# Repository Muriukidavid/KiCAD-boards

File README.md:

My KiCAD boards

These are not final
Mostly Arduino breakout boards and shields

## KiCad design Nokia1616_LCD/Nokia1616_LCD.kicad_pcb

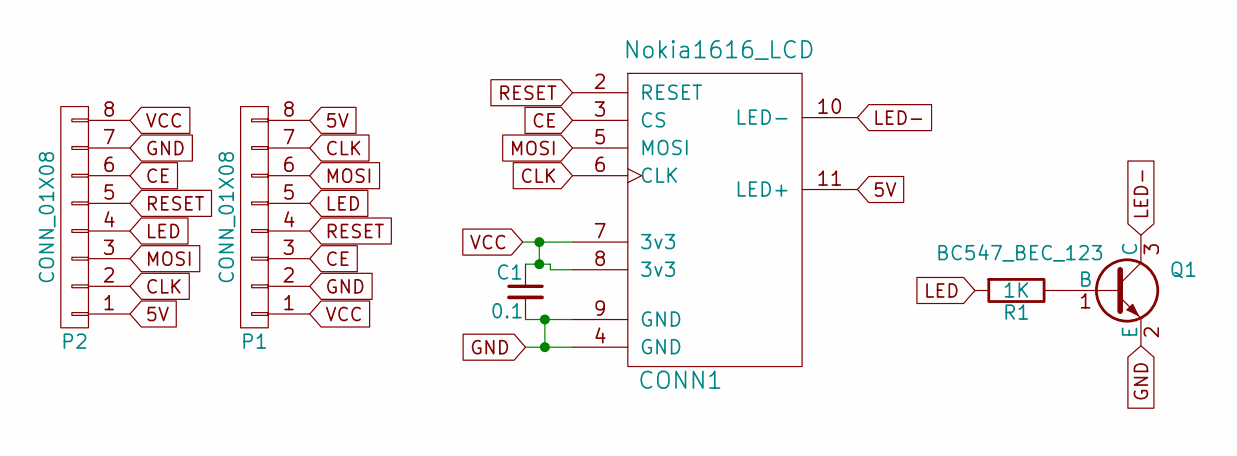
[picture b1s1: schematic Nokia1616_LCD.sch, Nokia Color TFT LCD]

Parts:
C1: 0.1; C_1206
CONN1: Nokia1616_LCD
P1, P2: CONN_01X08; Pin_Header_Straight_1x08_Pitch2.54mm
Q1: BC547_BEC_123; SOT-23
R1: 1K; R_1206

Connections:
5V: CONN1.11 (LED+), P1.8, P2.1
CE: CONN1.3 (CS), P1.3, P2.6
CLK: CONN1.6 (CLK), P1.7, P2.2
GND: C1.2, CONN1.4 (GND), CONN1.9 (GND), P1.2, P2.7, Q1.2 (E)
LED: P1.5, P2.4, R1.2
LED-: CONN1.10 (LED-), Q1.3 (C)
MOSI: CONN1.5 (MOSI), P1.6, P2.3
unnamed: Q1.1 (B), R1.1
RESET: CONN1.2 (RESET), P1.4, P2.5
VCC: C1.1, CONN1.7 (3v3), CONN1.8 (3v3), P1.1, P2.8

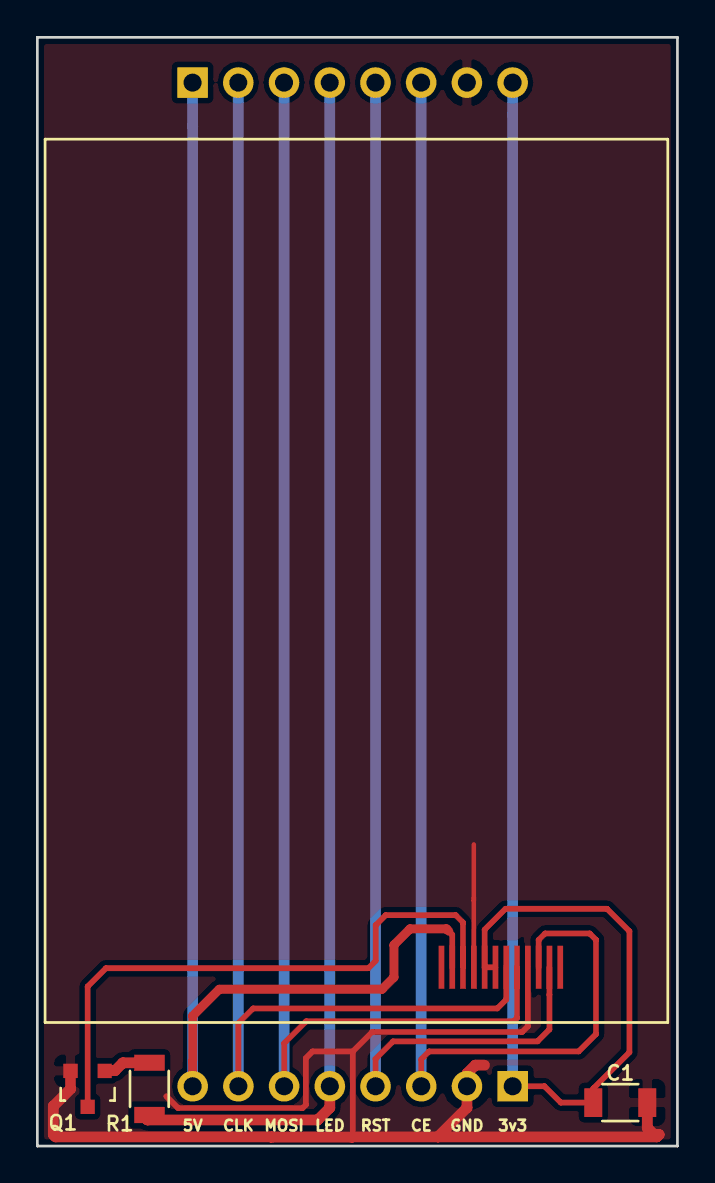
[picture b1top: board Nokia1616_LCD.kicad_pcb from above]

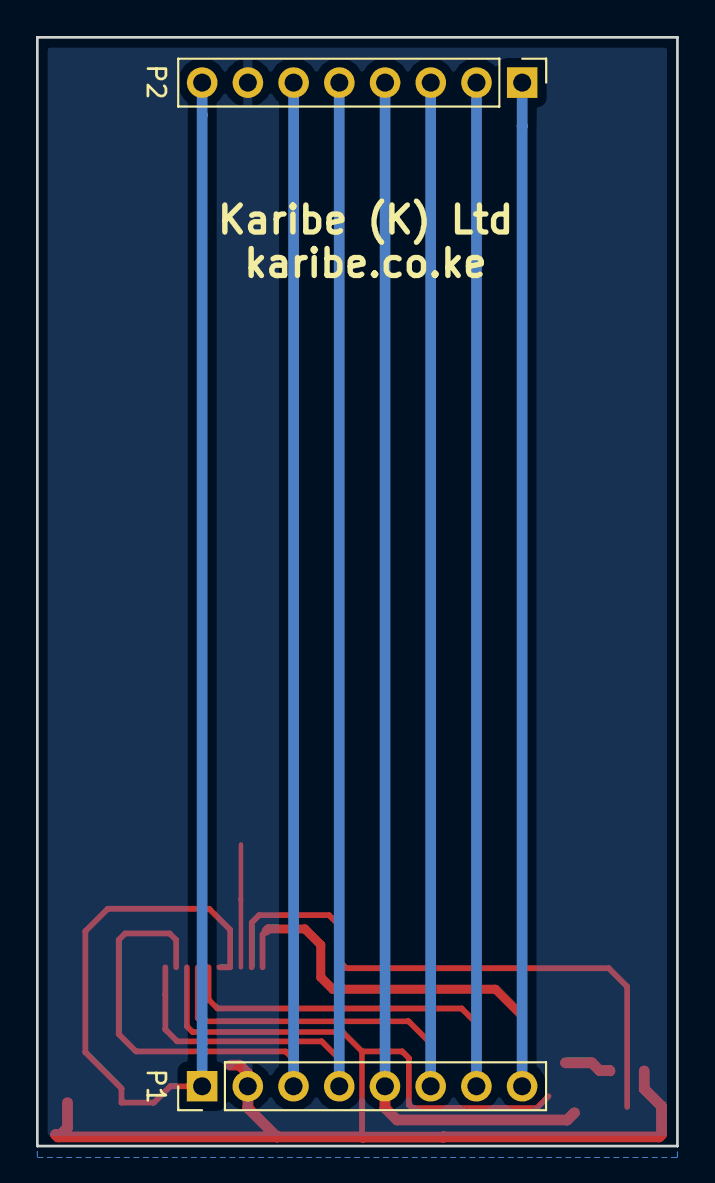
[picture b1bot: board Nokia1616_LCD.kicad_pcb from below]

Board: 2 copper layers, 35.6 x 61.6 mm, 6 parts (2 on the bottom side), 10 nets.

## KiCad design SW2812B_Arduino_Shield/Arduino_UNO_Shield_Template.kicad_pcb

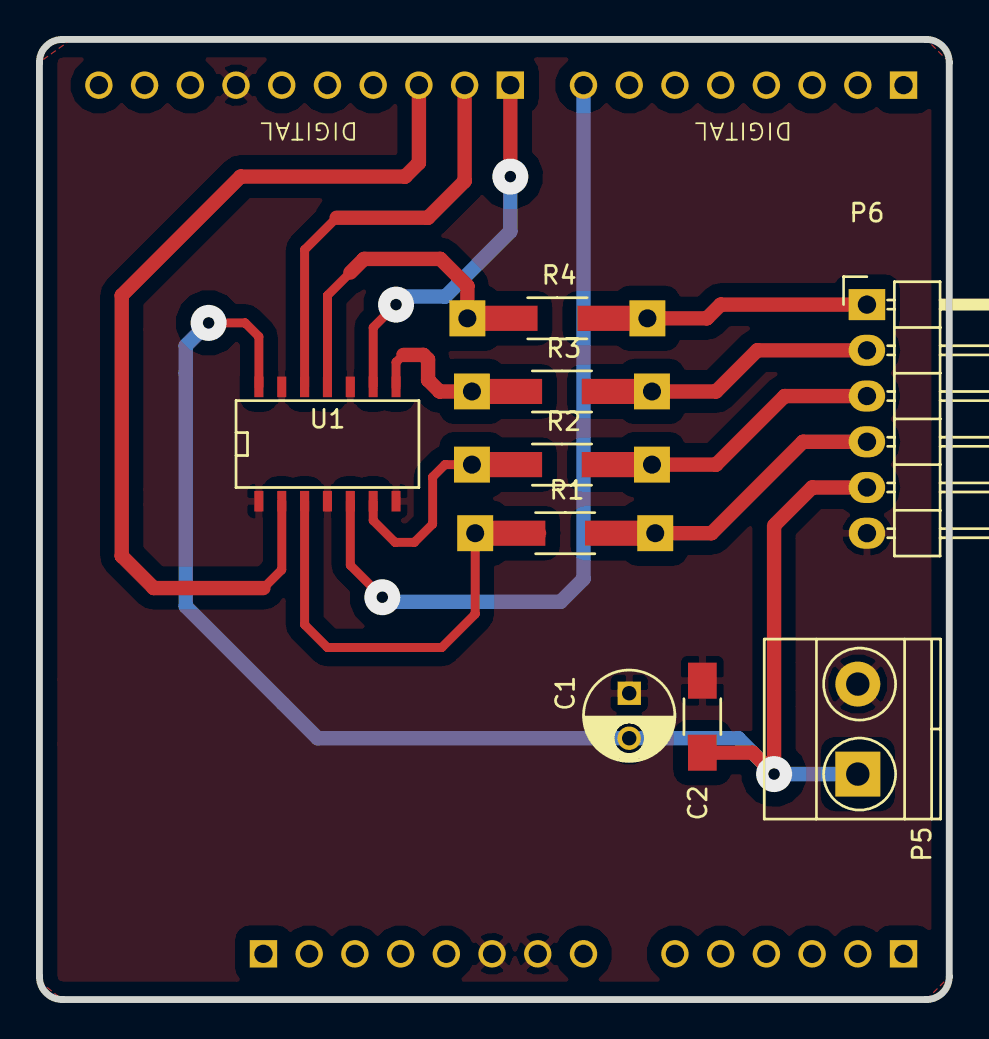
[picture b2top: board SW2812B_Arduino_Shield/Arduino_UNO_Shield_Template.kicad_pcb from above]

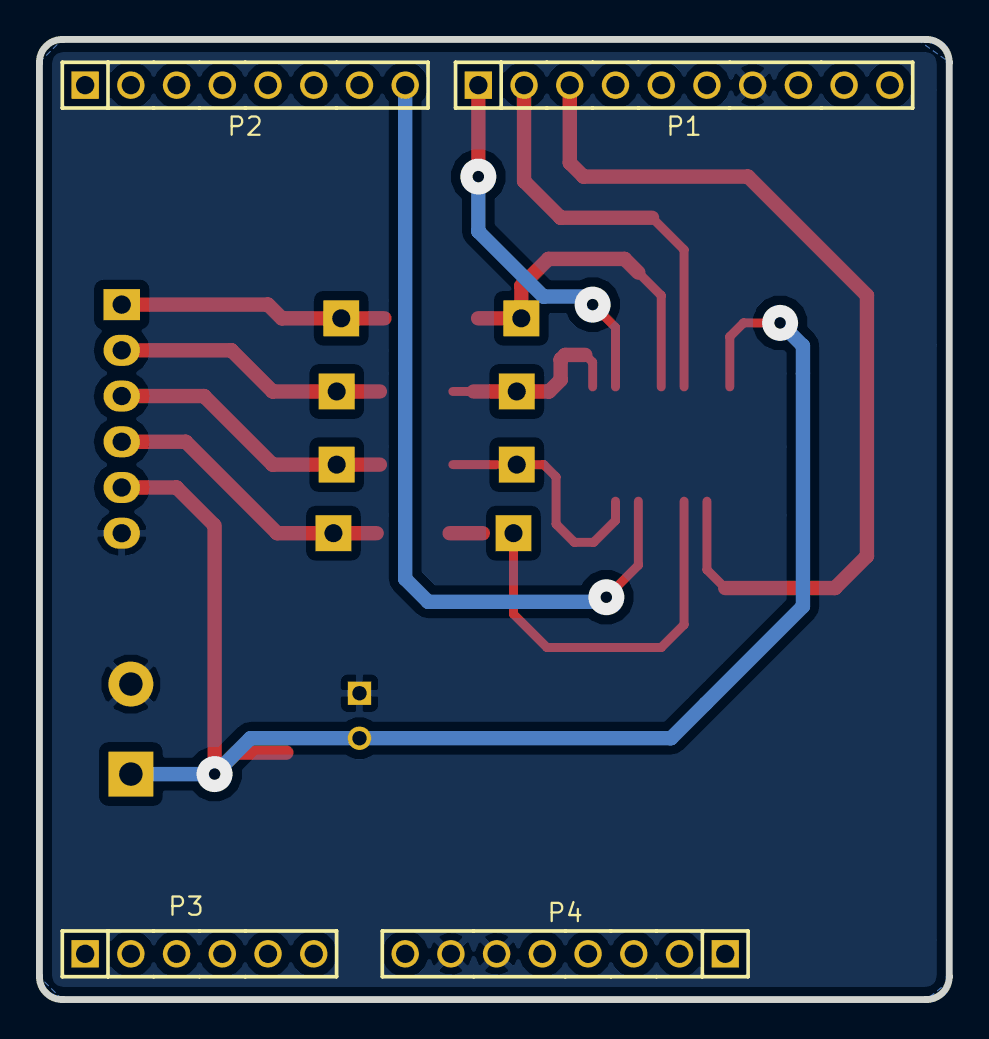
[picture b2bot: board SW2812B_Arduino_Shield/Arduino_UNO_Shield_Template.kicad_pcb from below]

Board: 2 copper layers, 50.5 x 53.3 mm, 13 parts (4 on the bottom side), 14 nets.

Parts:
C1: 1000uF; C_Radial_D5_L11_P2.5
C2: 1000uF; C_1206_HandSoldering
P1: HEADER_M_2.54MM_1R10P_ST_AU_PTH
P2, P4: HEADER_M_2.54MM_1R8P_ST_AU_PTH
P3: HEADER_M_2.54MM_1R6P_ST_AU_PTH
P5: CONN_01X02; TerminalBlock_Pheonix_MKDS1.5-2pol
P6: CONN_01X06; Pin_Header_Angled_1x06
R1, R2, R3, R4: R; Resistor_SMD+THTuniversal_1206_RM10_HandSoldering
U1: 74LS126; SOIC-14_N

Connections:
GND: C1.1, C2.1, P1.7, P4.6, P4.7, P5.2, P6.6, U1.1, U1.4, U1.7, U1.10, U1.13
IO7: P2.8, U1.5
IO8: P1.1, U1.9
IO9: P1.2, U1.12
IO10/SS: P1.3, U1.2
unnamed: P6.1, R4.2
unnamed: P6.2, R3.2
unnamed: P6.3, R2.2
unnamed: P6.4, R1.2
unnamed: R1.1, U1.3
unnamed: R2.1, U1.6
unnamed: R3.1, U1.8
unnamed: R4.1, U1.11
PWR: C1.2, C2.2, P5.1, P6.5, U1.14

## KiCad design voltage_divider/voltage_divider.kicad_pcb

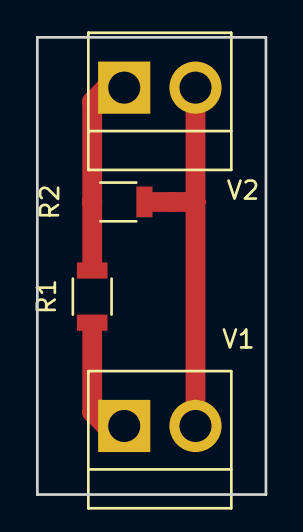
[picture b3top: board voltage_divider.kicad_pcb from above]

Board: 2 copper layers, 12.7 x 25.4 mm, 4 parts (0 on the bottom side), 3 nets.

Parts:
R1: 1k; R_1206
R2: 470; R_1206
V1, V2: DC 12; Pin_Header_Straight_1x02_Pitch3.96mm_Friction_Lock

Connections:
0: R2.2, V1.2, V2.2
Vin: R1.2, V1.1
Vout: R1.1, R2.1, V2.1

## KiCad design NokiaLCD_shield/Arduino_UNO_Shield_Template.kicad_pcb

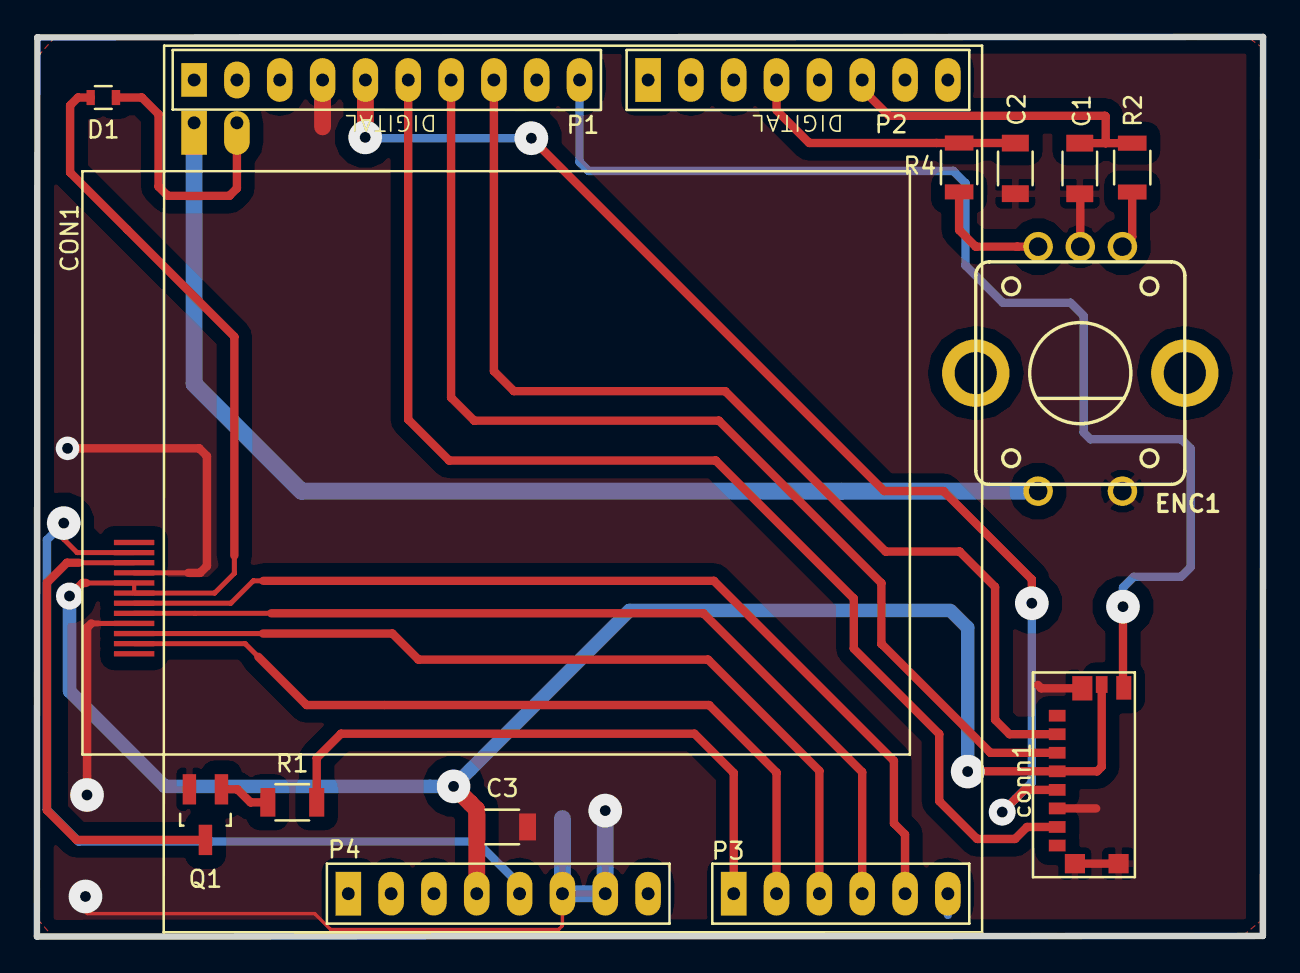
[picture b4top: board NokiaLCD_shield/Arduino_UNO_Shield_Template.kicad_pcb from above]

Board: 2 copper layers, 72.7 x 53.4 mm, 13 parts (1 on the bottom side), 21 nets.

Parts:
C1, C2, C3: 0.1uF; C_1206
CON1: Nokia1616_LCD
D1: LED; R_0603
ENC1: ALPS-STEC12E08; ROTARY_ENCODER_ALPS_STEC12E08
P1: CONN_01X02; Pin_Header_Straight_1x02
Q1: BC547_BEC_123; SOT-23_Handsoldering
R1: 1K; R_1206
R2, R4: 10K; R_1206
U1: ArduinoUnoR3
conn1: sdcard_475710001; MicroSDcard-475710001

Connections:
3.3V: C3.1, CON1.7, CON1.8, D1.2, U1.29, conn1.P4, conn1.P10
5V: CON1.11, U1.28
A: ENC1.A, R2.1
AD0: R1.2, U1.24
AD1: CON1.2, U1.23
AD2: CON1.3, U1.22
AD3: CON1.5, U1.21
AD4: CON1.6, U1.20
B: ENC1.B, R4.1
GND: C1.2, C2.2, C3.2, CON1.4, CON1.9, ENC1.C, ENC1.SW1, Q1.2, U1.4, U1.26, U1.27, conn1.P6, conn1.P9
IO2: C1.1, R2.2, U1.16
IO4: C2.1, R4.2, U1.14
IO8: U1.10, conn1.P11
IO10/SS: U1.8, conn1.P2
IO11/MOSI: U1.7, conn1.P3
IO12/MISO: U1.6, conn1.P7
IO13/SCK: U1.5, conn1.P5
LED: D1.1, P1.2
LED-: CON1.10, Q1.3
unnamed: ENC1.SW2, P1.1
unnamed: Q1.1, R1.1

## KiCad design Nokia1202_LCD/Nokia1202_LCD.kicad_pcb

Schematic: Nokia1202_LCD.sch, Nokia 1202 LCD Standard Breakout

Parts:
C1: 0.1u; CP_Tantalum_Case-A_EIA-3216-18_Wave
J1, J2, J3, J4: Conn_01x01; Pin_Header_Angled_1x01_Pitch2.54mm
LCD1: Nokia1202_LCD; Nokia1202LCD_folded
P1: CONN_01X08; Pin_Header_Straight_1x08
Q1: Q_NPN_BEC; SOT-23
R1: 1K; R_0805
R2: 680; R_0805

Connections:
CE: LCD1.3 (CS), P1.3
CLK: LCD1.6 (CLK), P1.7
GND: C1.2, LCD1.4 (GND), LCD1.9 (GND), P1.2, Q1.2 (E)
LED: P1.5, R1.1
LED-: LCD1.10 (LED-), Q1.3 (C)
MOSI: LCD1.5 (MOSI), P1.6
unnamed: LCD1.11 (LED+), R2.1
unnamed: Q1.1 (B), R1.2
RESET: LCD1.2 (Reset), P1.4
VCC: C1.1, LCD1.7 (3v3), LCD1.8 (3v3), P1.1, P1.8, R2.2

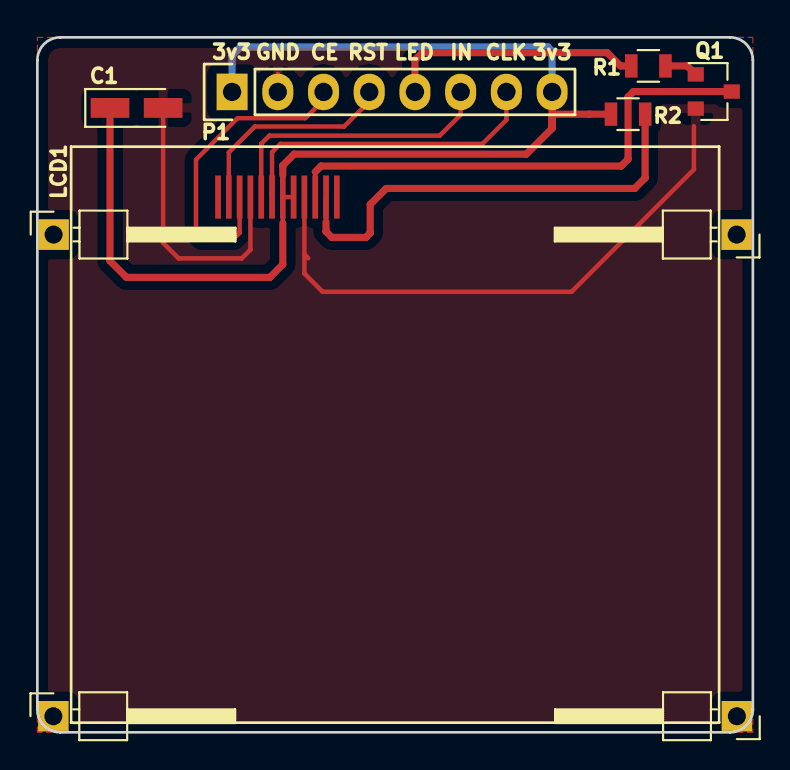
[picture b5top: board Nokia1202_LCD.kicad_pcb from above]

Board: 2 copper layers, 39.8 x 38.6 mm, 10 parts (0 on the bottom side), 10 nets.

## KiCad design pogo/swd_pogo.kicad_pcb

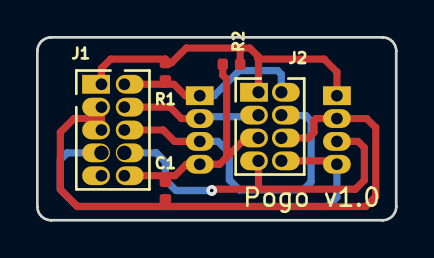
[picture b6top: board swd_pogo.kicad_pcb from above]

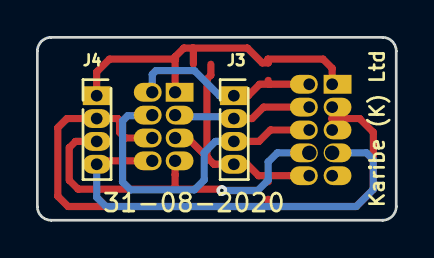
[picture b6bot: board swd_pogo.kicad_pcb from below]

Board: 2 copper layers, 19.9 x 10.2 mm, 7 parts (2 on the bottom side), 8 nets.

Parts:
C1: 100nF; C_0402_1005Metric
J1: CONN_02X05; Pin_Header_Straight_2x05_Pitch1.27mm
J2: Conn_02x04_Odd_Even; Pin_Header_Pogo_02x04_Pitch1.27mm
J3, J4: CONN_01X04; Pin_Header_Straight_01x04_Pitch1.27mm_wide
R1, R2: 10K; R_0402_1005Metric

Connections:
3v3: J1.1, J2.1, J4.1, R1.1, R2.2
GND: C1.2, J1.3, J1.5, J2.6, J4.2
RESET: C1.1, J1.10, J2.5, J3.4, R2.1
SWDCLK: J1.4, J2.3, J3.2
SWDIO: J1.2, J2.2, J3.1, R1.2
SWDTRACE: J1.6, J2.4, J3.3
UARTRX: J1.8, J2.7, J4.3
UARTTX: J1.7, J2.8, J4.4

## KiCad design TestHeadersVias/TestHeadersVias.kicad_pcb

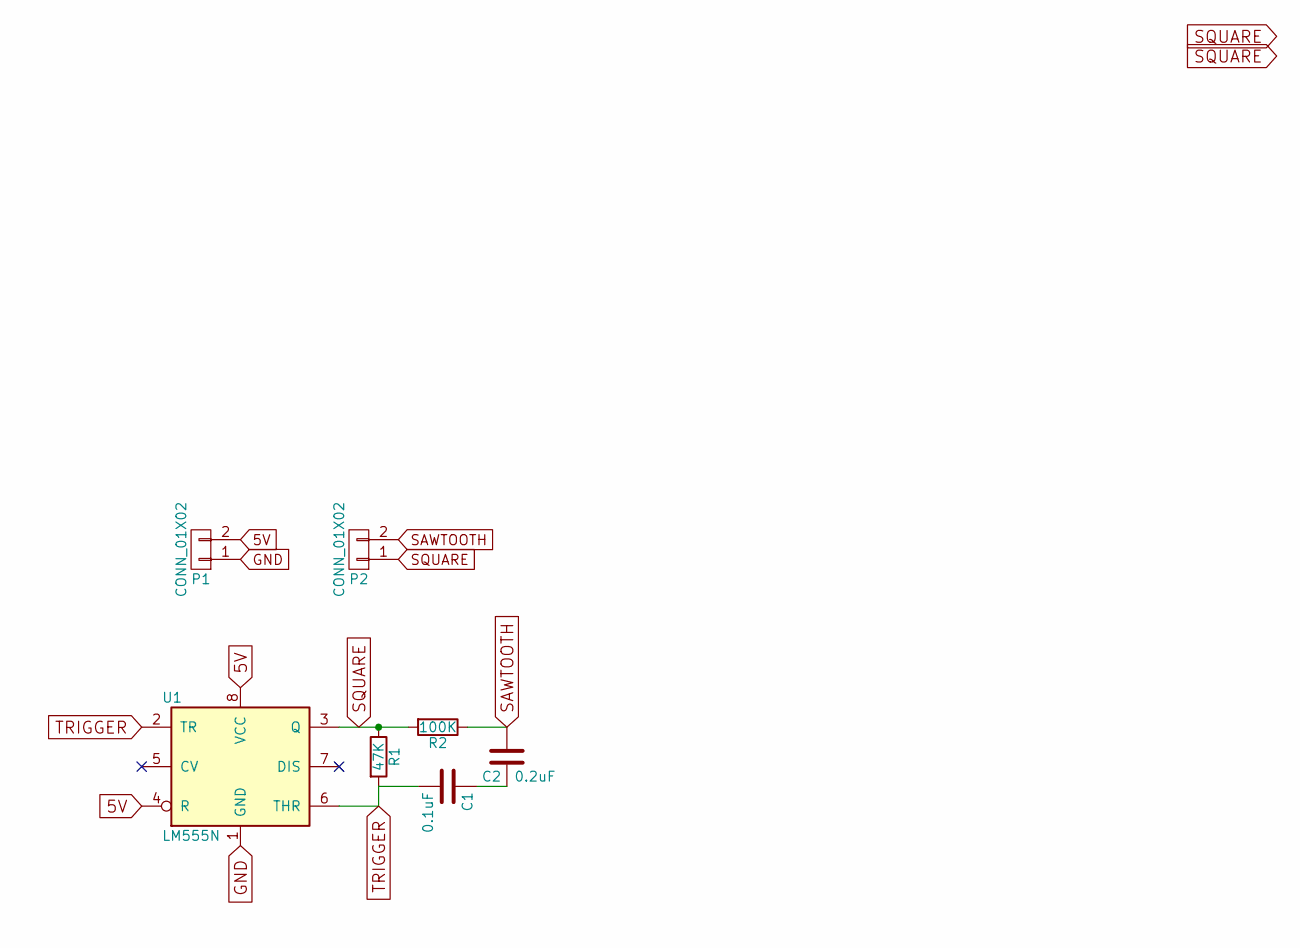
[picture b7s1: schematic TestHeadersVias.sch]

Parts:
C1: 0.1uF; C_0805
C2: 0.2uF; C_0805
P1, P2: CONN_01X02; Pin_Header_Straight_1x02
R1: 47K; R_1206
R2: 100K; R_1206
U1: LM555N; DIP-8_W7.62mm

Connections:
5V: P1.2, U1.4 (R), U1.8 (VCC)
GND: P1.1, U1.1 (GND)
unnamed: C1.1, C2.1
SAWTOOTH: C2.2, P2.2, R2.1
SQUARE: P2.1, R1.1, R2.2, U1.3 (Q)
TRIGGER: C1.2, R1.2, U1.2 (TR), U1.6 (THR)

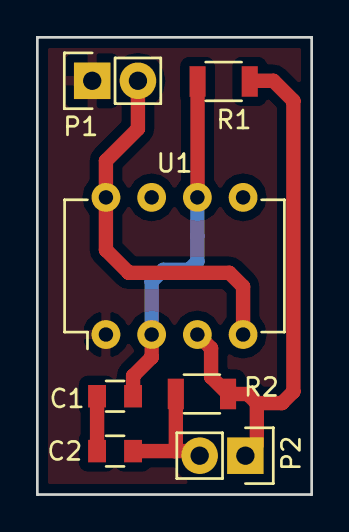
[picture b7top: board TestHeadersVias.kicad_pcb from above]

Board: 2 copper layers, 15.2 x 25.4 mm, 7 parts (0 on the bottom side), 6 nets.

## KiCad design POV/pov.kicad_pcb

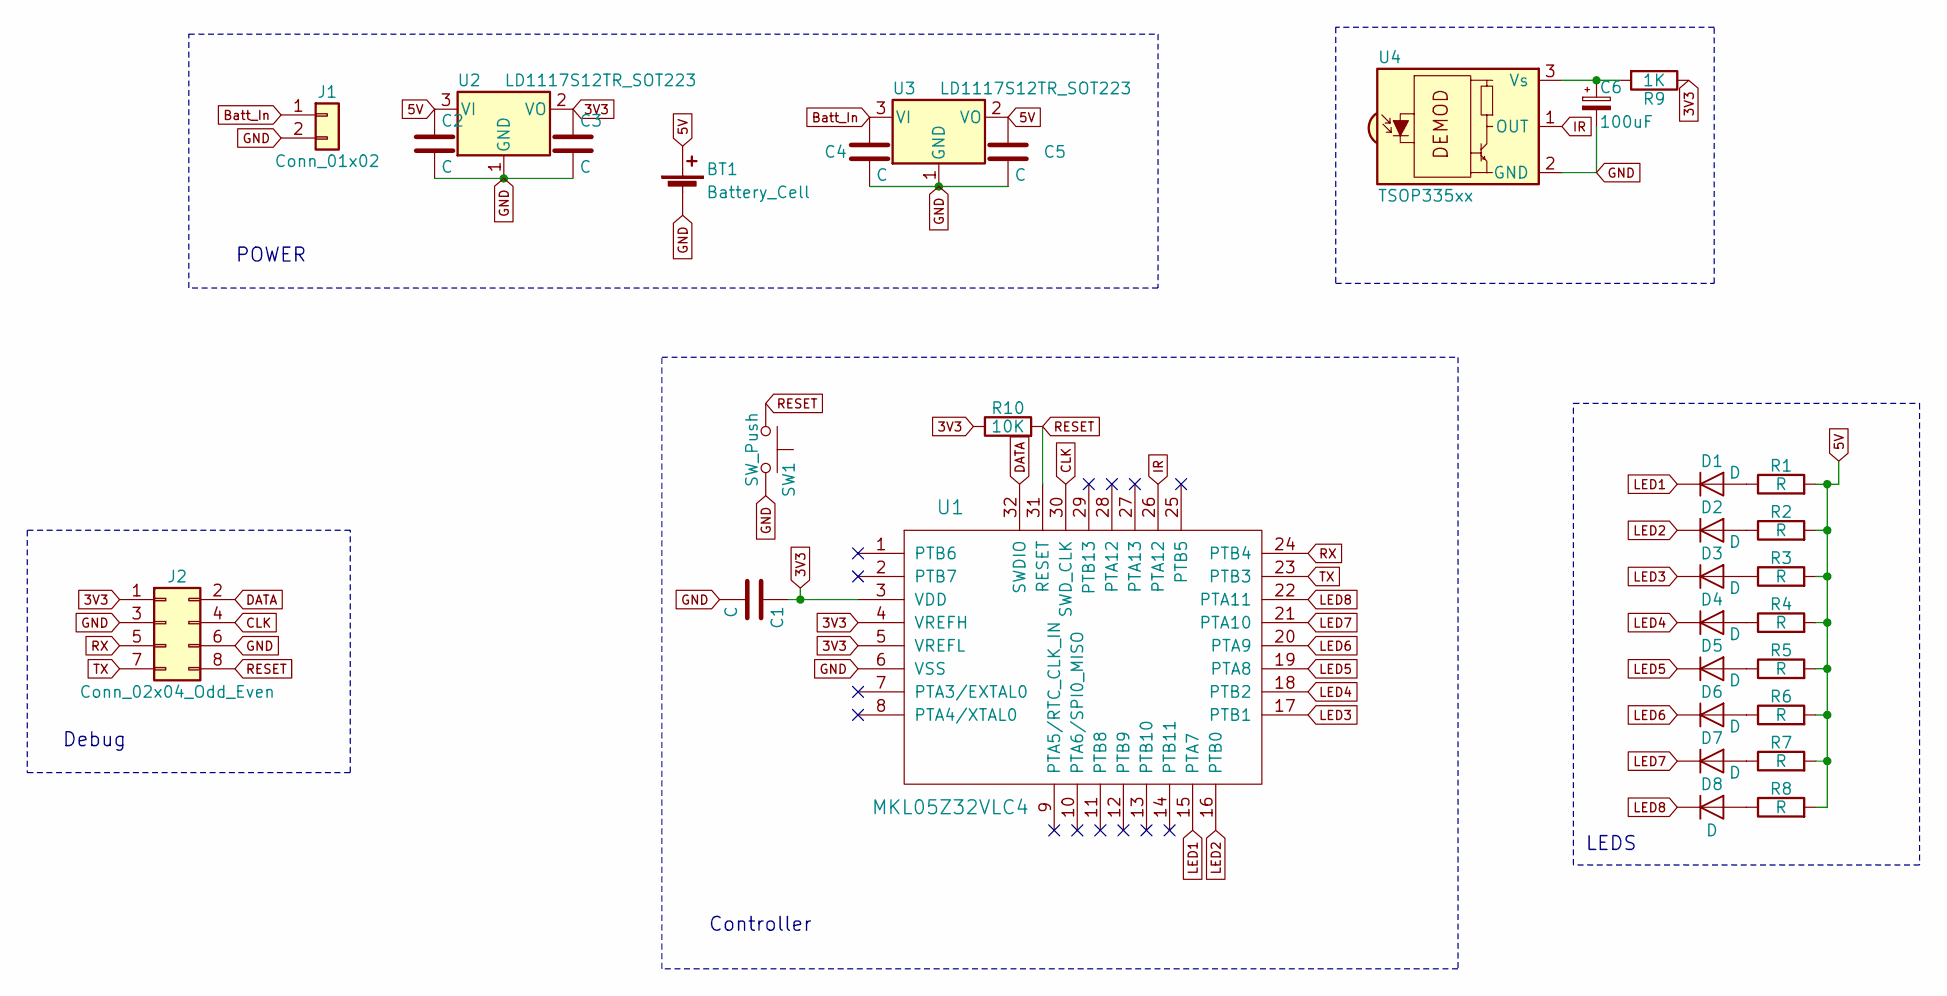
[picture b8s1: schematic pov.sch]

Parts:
BT1: Battery_Cell; Keystone_103_1x20mm-CoinCell
C1: C; C_0603
C2, C3, C4, C5: C; C_0805
C6: 100uF; C_0805
D1, D2, D3, D4, D5, D6, D7, D8: D; LED_0805
J1: Conn_01x02; Pin_Header_Angled_1x02
J2: Conn_02x04_Odd_Even; Pin_Header_Pogo_SMD_2x04_Pitch1.27mm
R1, R2, R3, R4, R5, R6, R7, R8: R; R_0805
R9: 1K; R_0805
R10: 10K; R_0805
SW1: SW_Push; SW_SPST_FSMSM
U1: MKL05Z32VLC4; LQFP-32_7x7mm_Pitch0.8mm
U2, U3: LD1117S12TR_SOT223; SOT-23
U4: TSOP335xx; LED-5MM-3

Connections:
3V3: C1.1, C3.1, J2.1, R9.1, R10.1, U1.3 (VDD), U1.4 (VREFH), U1.5 (VREFL), U2.2 (VO)
5V: BT1.1 (+), C2.1, C5.1, R1.2, R2.2, R3.2, R4.2, R5.2, R6.2, R7.2, R8.2, U2.3 (VI), U3.2 (VO)
Batt_In: C4.1, J1.1, U3.3 (VI)
CLK: J2.4, U1.30 (SWD_CLK)
DATA: J2.2, U1.32 (SWDIO)
GND: BT1.2 (-), C1.2, C2.2, C3.2, C4.2, C5.2, C6.2, J1.2, J2.3, J2.6, SW1.2, U1.6 (VSS), U2.1 (GND), U3.1 (GND), U4.2 (GND)
IR: U1.26 (PTA12), U4.1 (OUT)
LED1: D1.1 (K), U1.15 (PTA7)
LED2: D2.1 (K), U1.16 (PTB0)
LED3: D3.1 (K), U1.17 (PTB1)
LED4: D4.1 (K), U1.18 (PTB2)
LED5: D5.1 (K), U1.19 (PTA8)
LED6: D6.1 (K), U1.20 (PTA9)
LED7: D7.1 (K), U1.21 (PTA10)
LED8: D8.1 (K), U1.22 (PTA11)
unnamed: C6.1, R9.2, U4.3 (Vs)
unnamed: D1.2 (A), R1.1
unnamed: D2.2 (A), R2.1
unnamed: D3.2 (A), R3.1
unnamed: D4.2 (A), R4.1
unnamed: D5.2 (A), R5.1
unnamed: D6.2 (A), R6.1
unnamed: D7.2 (A), R7.1
unnamed: D8.2 (A), R8.1
RESET: J2.8, R10.2, SW1.1, U1.31 (RESET)
RX: J2.5, U1.24 (PTB4)
TX: J2.7, U1.23 (PTB3)

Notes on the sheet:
POWER
Debug
Controller
LEDS

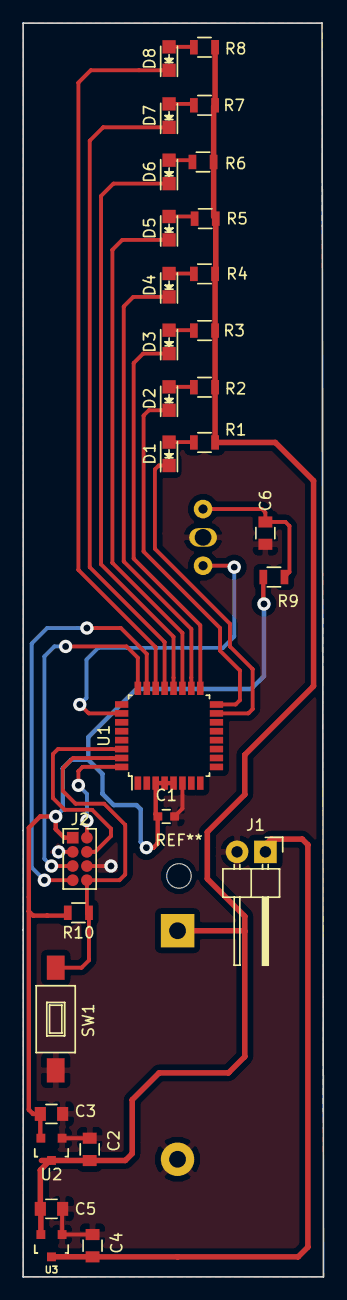
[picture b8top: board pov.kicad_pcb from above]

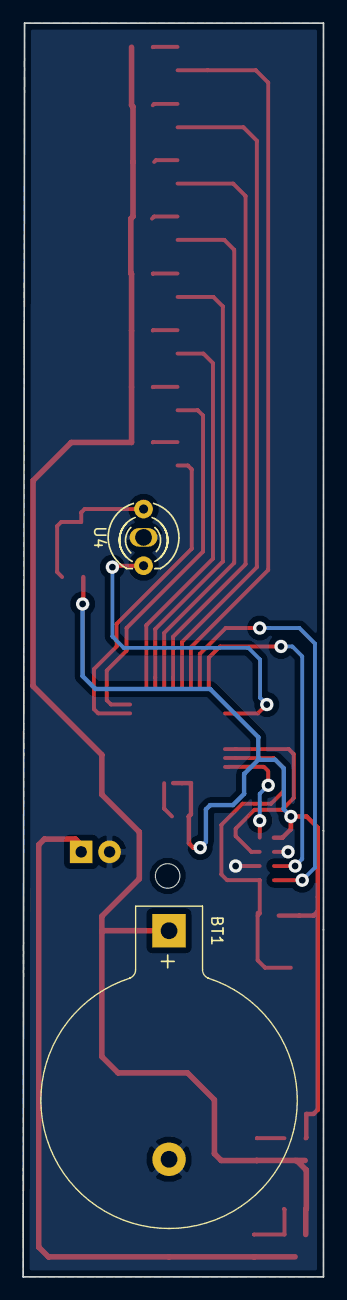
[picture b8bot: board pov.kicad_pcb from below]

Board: 2 copper layers, 26.9 x 112.4 mm, 32 parts (2 on the bottom side), 27 nets.

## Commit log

2017-02-07 Initial commit
    Add few spice simulations
    Add some Ardionu Uno R3 breakout for NxP Freedom boards
2017-02-22 Add arduino flex-sensor and SW2812B LED shields Add a folder for a flex-snsor arduino shield Add a folder for SW2812B LEDs arduino shield with a 4-channel 5v-3.3v levelshifter
2017-03-16 Changed Nokia1616 LCD backlight Added a low switch NPN transistor for PWM switching of backlight to ground Added a capacitor to ground on the 3v3 line Cleaned up the traces a bit
2017-10-11 Added Simulation Circuits and POV board
    Added a BJT characteristics simulation circuit
    Add a Voltage Divider simulation circuit
    Add an amplifier simulation circuit
    Add a Nokia LCD breakout board
    Add a POV LED MKL05Z board
2018-01-24 Re-rout PCB for Nokia1202 LCD breakout board
    Re-arrange the capacitor on vcc line and the 0ohm resistor on LED line
    Re-route the signals
    Add a bottom copper pour
    Make the power routes thicker[0.4mm]
    Resize the board smaller
    Export schematic[PDF] and PCB layout[SVG] for prototyping
2018-04-24 Clean up the simulation folders
    Remove a duplicate amplifier simulation project amplifier in favor of the opamp of the project
    Remove uneccesary files in the opamp
    Add a README.md to explain how to use the RC circuit simulation netlist file for the filter's characteristics and sample signal input and output
2018-04-24 Remove an unnecessary zipped file
2020-10-12 Too many untracked changes: LCD boards update and switch to KiCAD version 5
    Update the Nokia LCD breakout boards
    Add more KiCAD simulation projects
    Update most projects to KiCAD version 5
